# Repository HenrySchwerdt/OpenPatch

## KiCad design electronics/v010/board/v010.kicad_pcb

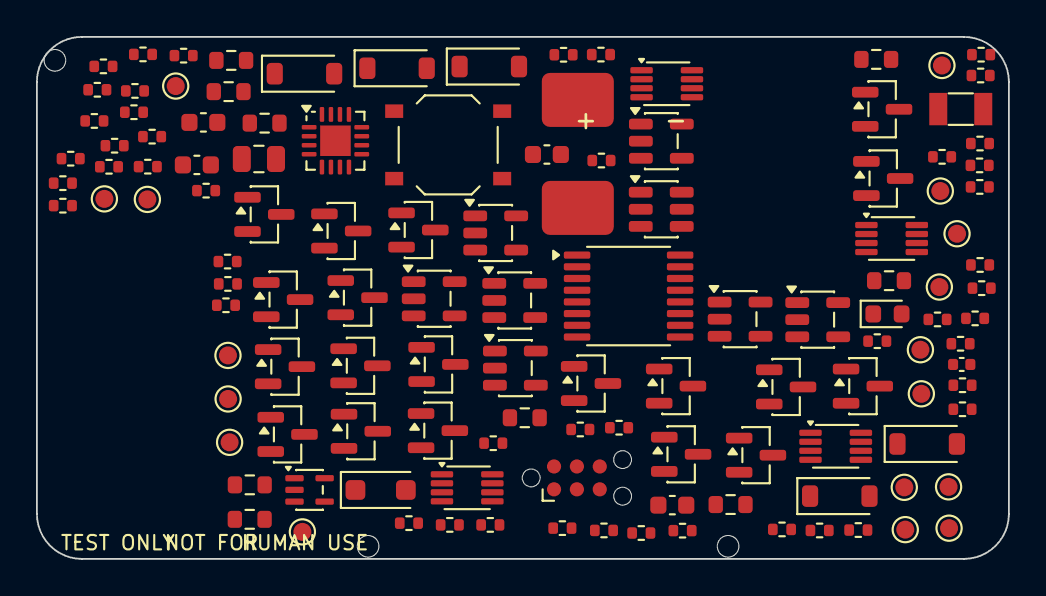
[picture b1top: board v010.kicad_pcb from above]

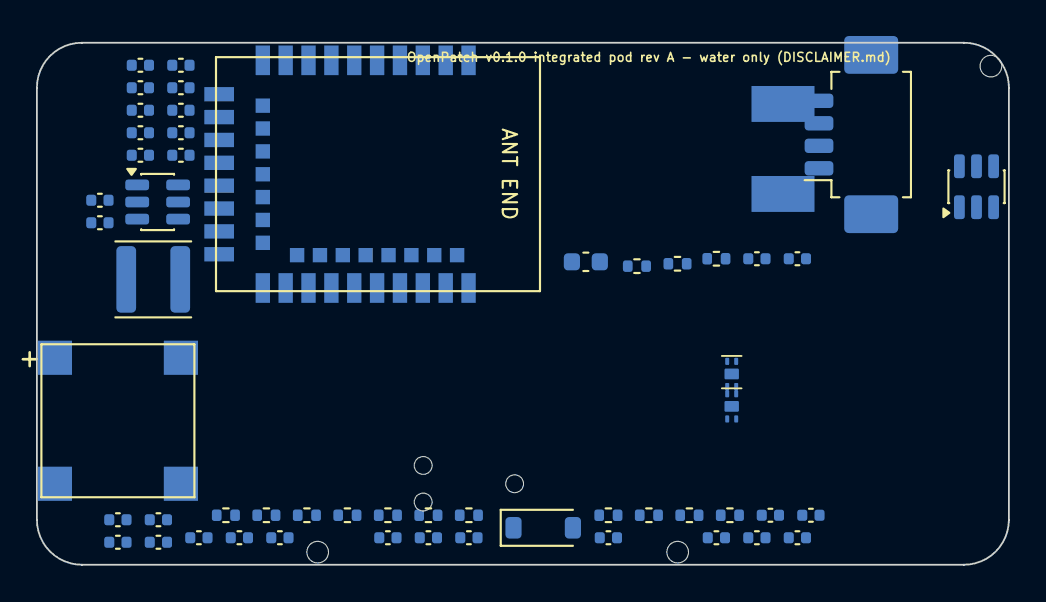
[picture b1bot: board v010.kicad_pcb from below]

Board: 4 copper layers, 54.0 x 29.0 mm, 185 parts (56 on the bottom side), 95 nets, no tracks yet.

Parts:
BZ1: MLT-8530; Buzzer_MLT-8530_8.5x8.5
C1, C10, C11, C14, C15, C19, C23, C25, C26, C28, C29, C30, C34, C35, C36, C37, C41, C42: 100nF; C_0402_1005Metric
C2, C8, C9: 4.7uF; C_0402_1005Metric
C3, C4: 15pF; C_0402_1005Metric
C5, C7, C22, C24: 10uF; C_0603_1608Metric
C6, C33: 1uF; C_0402_1005Metric
C16, C17, C20, C27, C32: 10nF; C_0402_1005Metric
C21: 22uF; C_0805_2012Metric
C31: 10uF (DNP); C_0603_1608Metric
D1, D5, D7: 1N4148W; D_SOD-123
D2, D4: B5819W SL; D_SOD-123
D3: SMF5.0A; D_SOD-123F
D6: B5819W SL (DNP); D_SOD-123
H1, H2, H3: NPTH 1.2; NPTH_1.2mm
J1: PicoBlade A1251WR-S-4P; Molex_PicoBlade_53261-0471_1x04-1MP_P1.25mm_Horizontal
J2: TC2030-IDC-NL (pads); Tag-Connect_TC2030-IDC-NL_2x03_P1.27mm_Vertical
L1: 4.7uH 4x4 (DNP); L_APV_ANR4018
LD1: red status; LED_0603_1608Metric
PAD1: charge pad +; Charge_Pad_4x3
PAD2: charge pad -; Charge_Pad_4x3
Q1, Q4, Q15: AO3401A; SOT-23
Q2, Q5, Q6, Q7, Q7B, Q8, Q10, Q11, Q12, Q13, Q14, Q16, Q17, Q18, Q19: 2N7002; SOT-23
R1, R5, R6, R7, R9, R10, R12, R15, R16, R17, R18, R21, R22, R28, R29, R32, R37, R39, R43, R46, R51, R53, R54, R57, R58, R61, R69, R72, R73: 100k; R_0402_1005Metric
R2, R70: 22R; R_0402_1005Metric
R3, R36: 47k; R_0402_1005Metric
R4: 3.3k; R_0402_1005Metric
R8, R11, R26, R40, R41, R42, R47, R48: 10k; R_0402_1005Metric
R13, R62: 0R; R_0603_1608Metric
R14, R33, R63: 0R DNP; R_0603_1608Metric
R19, R20: 4.7M; R_0402_1005Metric
R24, R25, R71, R75: 100R; R_0402_1005Metric
R27: 22k; R_0402_1005Metric
R30, R52, R74: 1k; R_0402_1005Metric
R31, R67, R68: 4.7k; R_0402_1005Metric
R34, R35: 1.0R; R_0603_1608Metric
R38: 5.1k; R_0402_1005Metric
R44: 0.22R; R_0603_1608Metric
R45: 0R bypass; R_0603_1608Metric
R49, R50, R59, R60: 1M; R_0402_1005Metric
R55: 220k (DNP); R_0402_1005Metric
R56: 30k (DNP); R_0402_1005Metric
RT1: NTC 10k NCP15XH103F03RC; C_0402_1005Metric
SP1, SP2: BWCD-L3.5W2.0H1.0 spring; Spring_Contact_3.5x2.0
SW1: TS-1187A-B-A-B; SW_Push_1P1T_XKB_TS-1187A
TP1: GND; TestPoint_Pad_D1.0mm
TP2: 3V3; TestPoint_Pad_D1.0mm
TP3: VBAT; TestPoint_Pad_D1.0mm
TP4: VMOT; TestPoint_Pad_D1.0mm
TP5: PGATE; TestPoint_Pad_D1.0mm
TP6: LATCH_Q; TestPoint_Pad_D1.0mm
TP7: MCU_EN; TestPoint_Pad_D1.0mm
TP8: DOCKED_H; TestPoint_Pad_D1.0mm
TP9: ARM_CLK; TestPoint_Pad_D1.0mm
TP10: LATCH_CLR_N; TestPoint_Pad_D1.0mm
TP11: NRST; TestPoint_Pad_D1.0mm
TP12: STCK_DRV; TestPoint_Pad_D1.0mm
TP13: WIN; TestPoint_Pad_D1.0mm
TP14: HWA_FULL; TestPoint_Pad_D1.0mm
TP15: OC_OK; TestPoint_Pad_D1.0mm
TP16: INA_OUT; TestPoint_Pad_D1.0mm
TP17: VCHG; TestPoint_Pad_D1.0mm
U1: E73-2G4M08S1C; Ebyte_E73-2G4M08S1C_13x18
U2: XC6206P332MR-G; SOT-23
U3: MCP73832T-2ACI/OT; SOT-23-5
U4A, U4B: DRV5032AJDMRR; DRV5032_X2SON-4_DMR0004B
U5: TPL5010DDCR; SOT-23-6
U6, U10, U12, U13: SN74AUP1G74DCUR; VSSOP-8_2.3x2mm_P0.5mm
U7: STSPIN220; QFN-16-1EP_3x3mm_P0.5mm_EP1.7x1.7mm
U8: MT3608 (DNP); SOT-23-6
U9: INA180A1IDBVR; SOT-23-5
U10T: TMAG5273A1QDBVR; SOT-23-6
U11: TLV7011DCKR; SOT-353_SC-70-5
U14: TP74AUP1G17S5; SOT-23-5
U15: SN74LV4040APWR; TSSOP-16_4.4x5mm_P0.65mm
U16, U18, U19: TP74AUP1G08S5; SOT-23-5
U17: TP74AUP1G32S5; SOT-23-5
Y1: 32.768kHz 12.5pF; Crystal_SMD_3215-2Pin_3.2x1.5mm

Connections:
3V3: C1.1, C2.1, C7.1, C14.1, C28.1, C29.1, C34.1, C35.1, C36.1, C37.1, C41.1, J2.1, R1.1, R12.1, R19.1, R20.1, R21.1, R28.2, R40.1, R49.1, R61.1, R67.1, R68.1, R69.1, R73.1, TP2.1, U1.19, U2.2, U4A.1, U4B.1, U5.1, U6.2, U6.7, U6.8, U10.7, U10.8, U10T.4, U11.5, U12.2, U12.7, U12.8, U13.2, U13.7, U13.8, U14.5, U15.16, U16.5, U17.5, U18.5, U19.5
ARM_CLK: R29.1, TP9.1, U1.32, U6.1, U13.1
BLD: Q17.3, R24.2, R25.2
BST_FB: R55.2, R56.1, U8.3
BST_SW: D6.2, L1.2, U8.1
BTN_N: C42.1, R73.2, SW1.1, U1.28
BUZ_PWM: R71.1, U1.38
BZ_D: Q19.3, R70.2
BZ_G: Q19.1, R71.2, R72.1
BZ_N: BZ1.2, D7.2, R70.1
CHG_P2: R3.2, R4.1
CHG_PAD: D3.1, PAD1.1, R2.1
CHG_PROG: R3.1, U3.5
CHG_R: D4.2, R2.2
CHG_STAT: U1.42, U3.1
CH_TOP: Q5.3, R11.2
CNT_CLK: U15.10, U19.4
DIR_INV: Q11.3, R12.2, R14.1, R62.1
DIR_REV: Q10.1, R13.2, R14.2, R15.1, U17.1
DOCKED_H: Q6.1, Q7.3, Q7B.3, Q12.3, R21.2, TP8.1, U1.10
DOCK_N: Q7.1, R19.2, U1.3, U4A.4
DOCK_NB: Q7B.1, R20.2, U4B.4
DOCK_TEST: Q12.1, R22.1, U1.2
DONE_PULSE: C16.2, R30.1, U10.1
DONE_TPL: R32.1, R33.2, U5.4, U10.5
FWD: R62.2, R63.2, U19.2
GND: C1.2, C2.2, C3.2, C4.2, C5.2, C6.2, C7.2, C8.2, C9.2, C10.2, C14.2, C15.2, C17.2, C19.2, C20.2, C21.2, C22.2, C23.2, C24.2, C25.2, C26.2, C27.2, C28.2, C29.2, C30.2, C31.2, C32.2, C33.2, C34.2, C35.2, C36.2, C37.2, C41.2, C42.2, D3.2, J2.5, PAD2.1, Q2.2, Q6.2, Q7.2, Q7B.2, Q10.2, Q11.2, Q12.2, Q14.2, Q16.2, Q17.2, Q18.2, Q19.2, R4.2, R7.2, R15.2, R16.2, R17.2, R18.2, R22.2, R26.2, R27.2, R29.2, R30.2, R32.2, R34.2, R35.2, R36.2, R38.2, R39.2, R41.2, R42.2, R43.2, R46.2, R51.2, R53.2, R56.2, R58.2, R72.2, R75.2, RT1.2, SP2.1, SW1.2, TP1.1, U1.5, U1.21, U1.24, U2.1, U3.2, U4A.2, U4A.5, U4B.2, U4B.5, U5.2, U6.4, U7.7, U7.17, U8.2, U9.2, U10.4, U10T.2, U10T.3, U11.2, U12.4, U13.4, U14.3, U15.8, U16.3, U17.3, U18.3, U19.3
HWA_FULL: Q18.1, TP14.1, U1.9, U15.2
HWA_FULL_N: Q18.3, R61.2, U16.2
HWA_X: U16.4, U17.2
HWA_Y: U17.4, U18.2
I2C_SCL: R68.2, U1.14, U10T.1
I2C_SDA: R67.2, U1.12, U10T.6
INA_OUT: R46.1, R47.1, R48.1, TP16.1, U9.1
I_SENSE: C26.1, R47.2, U1.7
LATCH_CLR_N: C15.1, D2.2, R28.1, TP10.1, U1.34, U6.6
LATCH_Q: Q5.1, R17.1, TP6.1, U1.33, U6.5
LD1_K: LD1.1, R75.1
LED_A: LD1.2, R74.2
LED_ST: R74.1, U1.36
MCU_EN: D5.1, Q8.1, R18.1, R54.1, TP7.1, U1.35
MODE1_L: R41.1, U7.16
MODE2_L: R42.1, U7.15
MOT_A1: J1.4, U7.3
MOT_A2: J1.2, U7.5
MOT_B1: J1.3, U7.10
MOT_B2: J1.1, U7.8
MOT_DIR: Q11.1, R13.1, R16.1, R63.1, U1.22, U7.1
MOT_EN_FAULT: C20.1, R40.2, U1.17, U7.13
MOT_REF: C19.1, R37.2, R38.1, U7.11
MOT_STBY: R37.1, R39.1, U1.1, U7.14
NRST: D2.1, J2.3, R1.2, TP11.1, U1.26, U5.6
NTC: R8.2, RT1.1, U1.8
OC_CLR_N: C30.1, D5.2, R54.2, U12.6
OC_CMP: U11.1, U12.1
OC_IN: C27.1, R48.2, U11.3
OC_OK: Q13.1, TP15.1, U1.41, U12.3
OC_REF: R49.2, R50.1, R52.2, U11.4
OC_REF2: R50.2, R51.1
OC_TEST: Q14.1, R53.1, U1.16
OC_TEST_D: Q14.3, R52.1
PGATE: C11.1, Q4.1, Q15.1, Q16.1, Q17.1, R9.2, R10.2, R11.1, TP5.1
PGATE_MON: Q16.3, U1.43
PG_MID1: Q5.2, Q8.3
PG_MID2: Q8.2, Q13.3
PG_MID2A: Q6.3, Q10.3, Q13.2
SENSE_EN: Q2.1, R8.1, U1.40
SNSA: R34.1, U7.4
SNSB: R35.1, U7.9
SP_G: Q1.1, Q2.3, R5.2
STCK_DRV: TP12.1, U7.2, U18.4, U19.1
STCK_MCU: R43.1, U1.20, U18.1
SWDCLK: J2.4, U1.39
SWDIO: J2.2, U1.37
TMAG_INT: R69.2, U10T.5
TN: C33.1, R59.2, R60.2, U14.2
TOFF: R36.1, U7.12
TS: U13.6, U14.4
VBAT: BZ1.1, C5.1, C6.1, C9.1, C11.2, D7.1, Q1.2, Q4.2, R5.1, R9.1, R10.1, SP1.1, TP3.1, U2.3, U3.3
VBAT_SENSE: C10.1, R6.2, R7.1, U1.15
VBAT_SW: Q1.3, R6.1
VCHG: C8.1, D4.1, TP17.1, U3.4
VMOT: C21.1, C22.1, C23.1, R24.1, R25.1, R44.2, R57.1, TP4.1, U7.6, U9.4
VMOT_A: Q4.3, Q15.2
VMOT_PRE: C31.1, D6.1, R44.1, R45.2, R55.1, U9.3
VMOT_RAW: C24.1, C25.1, L1.1, Q15.3, R45.1, U8.4, U8.5, U9.5
VMOT_SENSE: C32.1, R57.2, R58.1, U1.18
WAKE_CLR: C17.1, D1.1, R31.1, U10.6
WDT_DELAY: R26.1, R27.1, U5.3
WDT_DONE: C16.1, R33.1, U1.4
WDT_WAKE: D1.2, R31.2, U1.30, U5.5, U10.2
WIN: TP13.1, U1.6, U13.5, U16.1
WIN_N: R59.1, R60.1, U13.3, U15.11
XL1: C3.1, U1.11, Y1.1
XL2: C4.1, U1.13, Y1.2

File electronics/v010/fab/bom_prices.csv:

LCSC,Value,Qty/board,Unit USD (tier 1),JLC stock,Basic,Refs
C356849,E73-2G4M08S1C,1,7.6971,1,ext,U1
C1525,100nF,18,0.0024,34619114,basic,C1 C10 C11 C14 C15 C19 C23 C25 C26 C28 C29 C30 C34 C35 C36 C37 C41 C42
C23733,4.7uF,3,0.0077,983783,basic,C2 C8 C9
C32346,32.768kHz 12.5pF,1,0.15,663204,basic,Y1
C1548,15pF,2,0.0026,1413765,basic,C3 C4
C25741,100k,29,0.0009,8479183,basic,R1 R5 R6 R7 R9 R10 R12 R15 R16 R17 R18 R21 R22 R28 R29 R32 R37 R39 R43 R46 R51 R53 R54 R57 R58 R61 R69 R72 R73
C2826547,BWCD-L3.5W2.0H1.0 spring,2,0.0763,8081,ext,SP1 SP2
C19702,10uF,4,0.0167,10348979,basic,C5 C7 C22 C24
C5446,XC6206P332MR-G,1,0.138,429396,basic,U2
C52923,1uF,2,0.0055,9476015,basic,C6 C33
C193402,SMF5.0A,1,0.0284,453722,ext,D3
C25092,22R,2,0.001,4369824,basic,R2 R70
C8598,B5819W SL,2,0.0256,854955,basic,D4 D2
C38066,MCP73832T-2ACI/OT,1,0.9593,8016,ext,U3
C25792,47k,2,0.0019,5404806,basic,R3 R36
C25890,3.3k,1,0.0036,1526817,basic,R4
C15127,AO3401A,3,0.0855,1342147,basic,Q1 Q4 Q15
C8545,2N7002,15,0.0158,6047282,basic,Q2 Q5 Q8 Q13 Q6 Q10 Q11 Q7 Q7B Q12 Q16 Q17 Q14 Q18 Q19
C25744,10k,8,0.0015,35956809,basic,R8 R11 R26 R40 R41 R42 R47 R48
C77131,NTC 10k NCP15XH103F03RC,1,0.0164,292530,ext,RT1
C21189,0R,3,0.0021,15907781,basic,R13 R45 R62
C2152498,DRV5032AJDMRR,2,0.3744,0,ext,U4A U4B
C26091,4.7M,2,0.0008,9038,ext,R19 R20
C25076,100R,4,0.0012,10088994,basic,R24 R25 R71 R75
C473912,TPL5010DDCR,1,0.3536,59721,ext,U5
C25768,22k,1,0.001,1186378,basic,R27
C140267,SN74AUP1G74DCUR,4,0.6745,17358,ext,U6 U10 U12 U13
C15195,10nF,5,0.0037,5496842,basic,C16 C17 C20 C27 C32
C11702,1k,3,0.0013,29992555,basic,R30 R52 R74
C25900,4.7k,3,0.0017,12654925,basic,R31 R67 R68
C81598,1N4148W,3,0.0124,2921267,basic,D1 D5 D7
C2150516,STSPIN220,1,1.9612,270,ext,U7
C174300,1.0R,2,0.0029,150749,ext,R34 R35
C25905,5.1k,1,0.0014,4287672,basic,R38
C45783,22uF,1,0.1975,3628752,basic,C21
C225113,PicoBlade A1251WR-S-4P,1,0.1101,13833,ext,J1
C326952,0.22R,1,0.019,10537,ext,R44
C122228,INA180A1IDBVR,1,0.288,55831,ext,U9
C193688,TLV7011DCKR,1,0.5566,10273,ext,U11
C26083,1M,4,0.0011,2766372,basic,R49 R50 R59 R60
C49333201,TP74AUP1G17S5,1,0.0537,3000,ext,U14
C180412,SN74LV4040APWR,1,1.1901,271,ext,U15
C48886815,TP74AUP1G08S5,3,0.0603,1932,ext,U16 U18 U19
C49333203,TP74AUP1G32S5,1,0.0537,2930,ext,U17
C3716049,TMAG5273A1QDBVR,1,3.5703,3401,ext,U10T
C94599,MLT-8530,1,0.197,114212,ext,BZ1
C318884,TS-1187A-B-A-B,1,0.0215,757186,basic,SW1
C2286,red status,1,0.0077,8591521,basic,LD1

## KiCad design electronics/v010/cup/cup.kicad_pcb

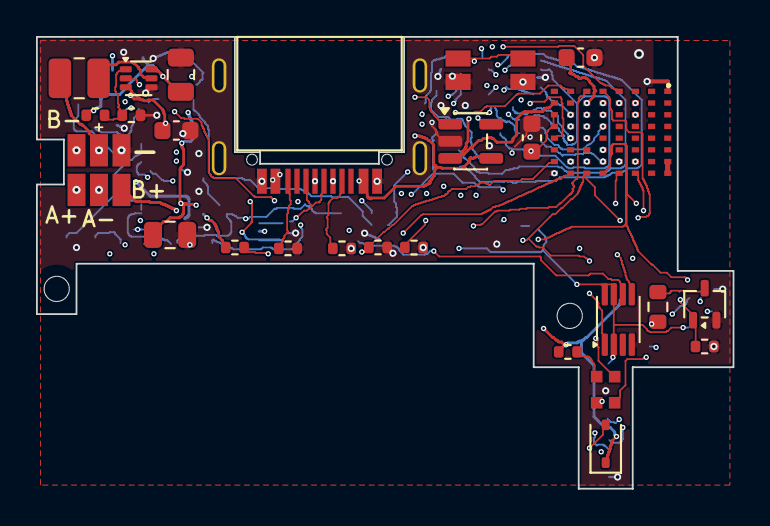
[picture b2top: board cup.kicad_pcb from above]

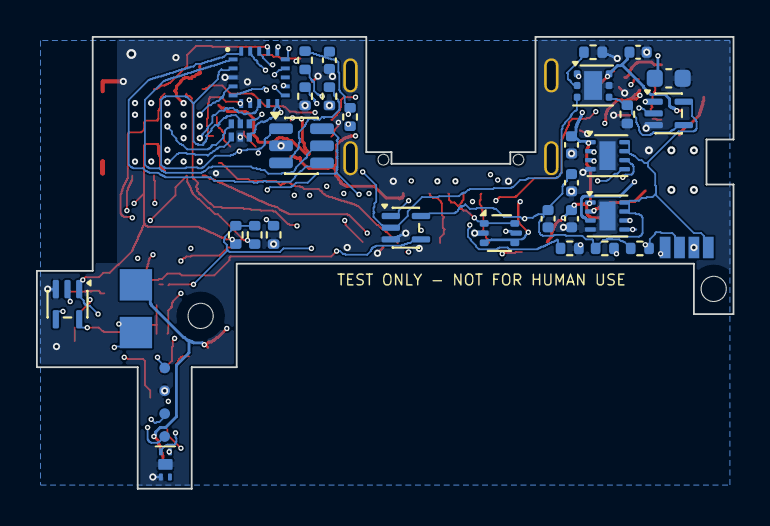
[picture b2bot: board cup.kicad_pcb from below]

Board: 6 copper layers, 38.7 x 25.1 mm, 72 parts (39 on the bottom side), 57 nets.

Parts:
BZ1: FUET-4020 SMD magnetic sounder; BZ_4020
C5: 10uF; C_0603_1608Metric
C19, C20, C50, C60, C61, C62: 100nF; C_0402_1005Metric
C21: 22uF; C_0805_2012Metric
C70: 4.7uF 16V 0603; C_0603_1608Metric
C71: 10uF 10V 0603; C_0603_1608Metric
CB1: 22uF 25V X5R 0805; C_0805_2012Metric
CU1: 10uF; C_0603_1608Metric
D6: 1N4148WS (sounder flyback); D_SOD-323
H1, H2: screw hole d1.4
JU1: USB-C 16P sink-board TYPE-C-31-M-14; USB_C_HRO_31_M_14
L1: 1uH 2520 (WPN252012E1R0MT); L_1008_2520Metric
LD1: RGB LED SZYY1615RGB-B (common anode); LED_RGB_1615_4P
MP1: motor lead pad A+; Wire_Pad_1.0x1.8
MP2: motor lead pad A-; Wire_Pad_1.0x1.8
MP3: motor lead pad B+; Wire_Pad_1.0x1.8
MP4: motor lead pad B-; Wire_Pad_1.0x1.8
QBA: 2N7002W; SOT-323_SC-70
R3, R91: 47k; R_0402_1005Metric
R16, R18, R29, R82, R90, R92: 100k; R_0402_1005Metric
R26: 6.8k; R_0402_1005Metric
R55: 220k; R_0402_1005Metric
R56: 30k; R_0402_1005Metric
R57, R58: 10k; R_0402_1005Metric
R74: 1k; R_0402_1005Metric
RBZ: 22R 0603; R_0603_1608Metric
RDA: 100k; R_0402_1005Metric
RDK: 100k; R_0402_1005Metric
RI1, RI2: 4.7k; R_0402_1005Metric
RNR: 100k; R_0402_1005Metric
RU1, RU2: 5.1k; R_0402_1005Metric
SP1: cell lead pad +; Wire_Pad_1.0x1.8
SP2: cell lead pad -; Wire_Pad_1.0x1.8
SW1: SKSCLAE010 side tact; SW_SKSCLAE010
TL1: REAR strip pad (3V3); FPC_Pad_1.2x0.6
TL2: REAR strip pad (GND); FPC_Pad_1.2x0.6
TL3: REAR strip pad (I2C_SDA); FPC_Pad_1.2x0.6
TL4: REAR strip pad (I2C_SCL); FPC_Pad_1.2x0.6
TPR1: recovery pad SWDIO; TP_Pad_D0.6
TPR2: recovery pad SWDCLK; TP_Pad_D0.6
TPR3: recovery pad GND; TP_Pad_D0.6
TPR4: recovery pad 3V3; TP_Pad_D0.6
U1: HJ-840 nRF52840 SiP; HJ840
U3: MCP73832T-2ACI/OT; SOT-23-5
U4A: DRV5032FADMRR; DRV5032_X2SON-4_DMR0004B
U5: TPL5010DDCR; SOT-23-6
U6: SN74AUP1G74DCUR; VSSOP-8_2.3x2mm_P0.5mm
U7A, U7B: DRV8838DSGR; Texas_DSG0008A_WSON-8-1EP_2x2mm_P0.5mm_EP0.9x1.6mm
U8: TPS61023DRLR; SOT-563
U20: TPS2553DRVR; WSON-6-1EP_2x2mm_P0.65mm_EP1x1.6mm
U30: STM32C011F4U6; UFQFPN-20_3x3_P0.5
U32, U34: SN74AUP1G08DCKR (AND); SOT-353_SC-70-5
U33: 74AUP1G86GW-TP (XOR); SOT-353_SC-70-5
U36: EM74AUP1G11GM (AND3); UFDFN-6_1.45x1.0_P0.5
UU1: USBLC6-2P6; SOT-666

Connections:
3V3: C19.1, C20.1, C50.1, C70.1, R16.1, R92.1, RDK.1, RI1.1, RI2.1, RNR.1, TL1.1, TPR4.1, U1.H3, U1.H4, U4A.1, U5.1, U6.2, U6.7, U6.8, U7A.7, U7A.8, U7B.7, U7B.8, U30.2, U32.5, U33.5, U34.5, U36.5
AENBL: U1.F5, U7A.5
ANT: U1.A7, U1.A8
APHASE: U1.H5, U7A.6, U30.6
ARM_CLK: R29.1, U1.G7, U6.1, U30.5
BENBL: U1.E6, U7B.5
BPHASE: U1.F4, U7B.6, U30.16
BST_FB: R55.2, R56.1, U8.1
BST_SW: L1.2, U8.5
BTN_N: SW1.1, SW1.2, U1.D2
BUZ_A: QBA.1, RDA.1, U1.C7
CC1: JU1.A5, RU1.1
CC2: JU1.B5, RU2.1
CHG_PROG: R3.1, U3.5
CHG_STAT: U1.G4, U3.1
DOCK_N: RDK.2, U1.E8, U4A.4, U30.18, U33.1
DOCK_XOR: U33.4, U34.2
GND: C5.2, C19.2, C20.2, C21.2, C50.2, C60.2, C61.2, C62.2, C70.2, C71.2, CB1.2, CU1.2, JU1.A1B12, JU1.B1A12, JU1.S, QBA.2, R3.2, R18.2, R26.2, R29.2, R56.2, R58.2, R82.2, R90.2, R91.2, RDA.2, RU1.2, RU2.2, SP2.1, SW1.3, SW1.4, TL2.1, TPR3.1, U1.A1, U1.H8, U3.2, U4A.2, U4A.5, U5.2, U6.4, U7A.4, U7A.9, U7B.4, U7B.9, U8.4, U20.5, U20.7, U30.3, U32.3, U33.3, U34.3, U36.2, UU1.2
I2C_SCL: RI2.2, TL4.1, U1.G8
I2C_SDA: RI1.2, TL3.1, U1.F7
ILIM: R91.1, U20.2
LATCH_CLR_N: U6.6, U32.4
LATCH_Q: U1.E7, U6.5, U36.1
LED_A: LD1.4, R74.2
LED_B: LD1.3, U1.D7
LED_G: LD1.2, U1.C8
LED_R: LD1.1, U1.D8
MCU_EN: R18.1, U1.E4, U30.19, U36.6
MOT_A1: MP1.1, U7A.2
MOT_A2: MP2.1, U7A.3
MOT_ALLOW: R90.1, U20.4, U34.4
MOT_B1: MP3.1, U7B.2
MOT_B2: MP4.1, U7B.3
MOT_FWD: R16.2, U1.F8, U30.7, U33.2
NRST: U1.E1, U30.12
OC_OK: R92.2, U1.G5, U20.3, U30.8, U32.2
PERM_L: U34.1, U36.4
PZ_A: QBA.3, RBZ.2
PZ_C: BZ1.2, D6.2, RBZ.1
SUP_BOOT0: U1.D1, U30.17
SUP_DONE: U5.4, U30.20
SUP_NRST: RNR.2, U1.G3, U5.6, U30.4, U32.1
SUP_OK: U1.F3, U30.11
SUP_PERMIT: R82.1, U8.2, U30.10, U36.3
SUP_RXD: U1.E2, U30.15
SUP_TXD: U1.E3, U30.14
SUP_WAKE: U5.5, U30.1
SWDCLK: TPR2.1, U1.C3
SWDIO: TPR1.1, U1.C2
USB_DM: JU1.A7, JU1.B7, U1.G1, UU1.3, UU1.4
USB_DP: JU1.A6, JU1.B6, U1.F1, UU1.1, UU1.6
VBAT: BZ1.1, C5.1, C71.1, D6.1, L1.1, R74.1, SP1.1, U1.H2, U3.3, U8.3
VBUS_P: CU1.1, JU1.A4B9, JU1.B4A9, U1.F2, U3.4, UU1.5
VMOT: C21.1, C61.1, C62.1, R57.1, U7A.1, U7B.1, U20.1
VMOT_PRE: C60.1, CB1.1, R55.1, U8.6, U20.6
VMOT_SENSE: R57.2, R58.1, U1.H7
WDT_DELAY: R26.1, U5.3

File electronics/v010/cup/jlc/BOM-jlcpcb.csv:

Comment,Designator,Footprint,LCSC Part #
FUET-4020 SMD magnetic sounder,BZ1,BZ_4020,C391027
10uF,"C5,C71,CU1",C_0603_1608Metric,C19702
100nF,"C19,C20,C50,C60,C61,C62",C_0402_1005Metric,C1525
22uF,"C21,CB1",C_0805_2012Metric,C45783
4.7uF 16V 0603,C70,C_0603_1608Metric,C19666
1N4148WS (sounder flyback),D6,D_SOD-323,C2128
USB-C 16P sink-board TYPE-C-31-M-14,JU1,USB_C_HRO_31_M_14,C223907
1uH 2520 (WPN252012E1R0MT),L1,L_1008_2520Metric,C370610
RGB LED SZYY1615RGB-B (common anode),LD1,LED_RGB_1615_4P,C3029071
2N7002W,QBA,SOT-323_SC-70,C232391
47k,"R3,R91",R_0402_1005Metric,C25792
100k,"R16,R18,R29,R82,R90,R92,RDA,RDK,RNR",R_0402_1005Metric,C25741
6.8k,R26,R_0402_1005Metric,C25917
220k,R55,R_0402_1005Metric,C25767
30k,R56,R_0402_1005Metric,C25776
10k,"R57,R58",R_0402_1005Metric,C25744
1k,R74,R_0402_1005Metric,C11702
22R 0603,RBZ,R_0603_1608Metric,C23345
4.7k,"RI1,RI2",R_0402_1005Metric,C25900
5.1k,"RU1,RU2",R_0402_1005Metric,C25905
SKSCLAE010 side tact,SW1,SW_SKSCLAE010,C130445
HJ-840 nRF52840 SiP,U1,HJ840,C50052094
MCP73832T-2ACI/OT,U3,SOT-23-5,C38066
TPL5010DDCR,U5,SOT-23-6,C473912
SN74AUP1G74DCUR,U6,VSSOP-8_2.3x2mm_P0.5mm,C140267
TPS61023DRLR,U8,SOT-563,C919459
TPS2553DRVR,U20,WSON-6-1EP_2x2mm_P0.65mm_EP1x1.6mm,C138719
STM32C011F4U6,U30,UFQFPN-20_3x3_P0.5,C5456188
SN74AUP1G08DCKR (AND),"U32,U34",SOT-353_SC-70-5,C507223
74AUP1G86GW-TP (XOR),U33,SOT-353_SC-70-5,C48995440
EM74AUP1G11GM (AND3),U36,UFDFN-6_1.45x1.0_P0.5,C54929506
DRV5032FADMRR,U4A,DRV5032_X2SON-4_DMR0004B,C2152496
DRV8838DSGR,"U7A,U7B",Texas_DSG0008A_WSON-8-1EP_2x2mm_P0.5mm_EP0.9x1.6mm,C86667
USBLC6-2P6,UU1,SOT-666,C2827693

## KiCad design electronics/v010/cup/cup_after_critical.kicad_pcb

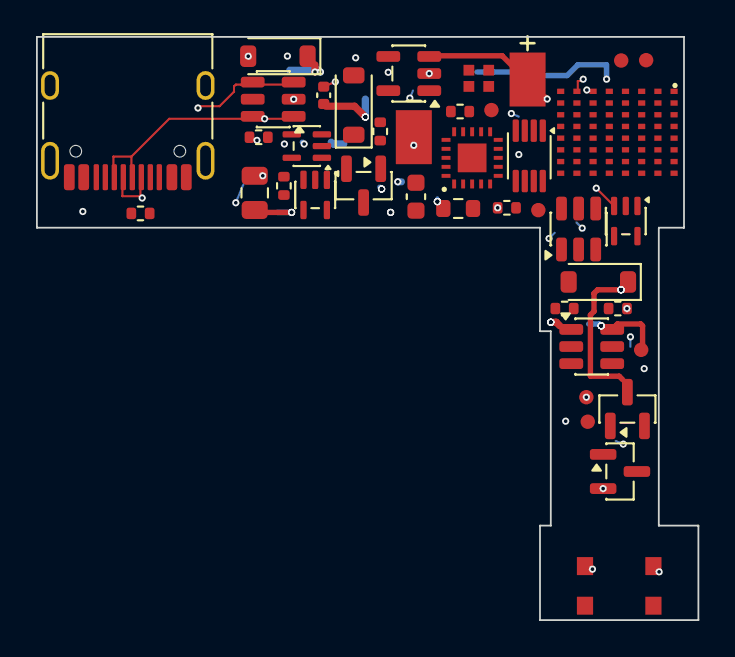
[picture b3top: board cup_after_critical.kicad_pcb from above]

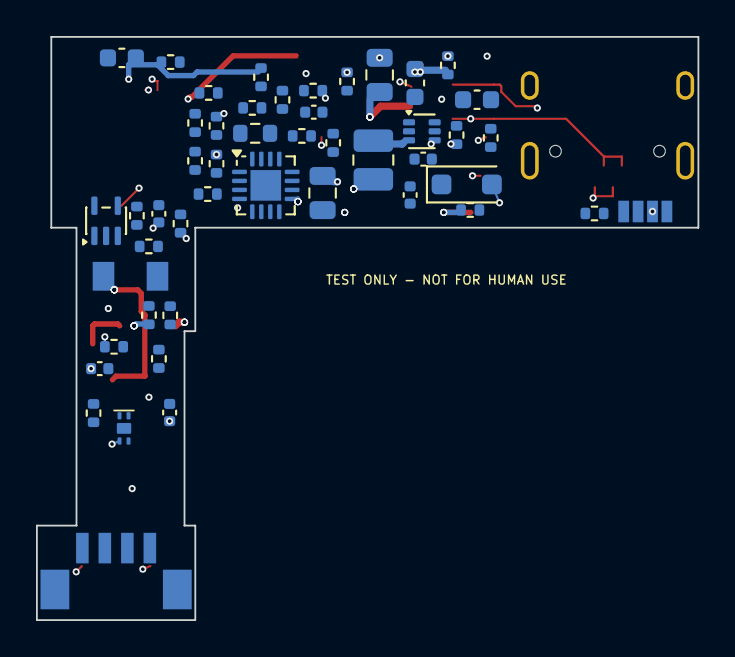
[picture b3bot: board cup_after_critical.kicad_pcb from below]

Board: 6 copper layers, 36.8 x 32.4 mm, 91 parts (51 on the bottom side), 63 nets.

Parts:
BZ1: FUET-4020 SMD magnetic sounder; BZ_4020
C1, C10, C19, C50, C60: 100nF; C_0402_1005Metric
C5, C7, C31: 10uF; C_0603_1608Metric
C21: 22uF; C_0805_2012Metric
CB1, CB2: 22uF 6.3V X5R 0805; C_0805_2012Metric
CU1: 10uF; C_0603_1608Metric
D5: 1N4148W; D_SOD-123
D6: 1N4148W (sounder flyback); D_SOD-123
DU1: SMF5.0A TVS; D_SOD-123F
DZ1: BZT52C6V2 (VMOT overvoltage clamp); D_SOD-123
J1: PicoBlade A1251WR-S-4P (CJT, plug of the NFP-608 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; A1251WR-S-4P
J10: SWD pad SWDIO; TP_Pad_D0.8
J11: SWD pad SWDCLK; TP_Pad_D0.8
J12: SWD pad NRST; TP_Pad_D0.8
J13: SWD pad GND; TP_Pad_D0.8
J14: SWD pad 3V3; TP_Pad_D0.8
JU1: USB-C receptacle (proxy: TYPE-C-31-M-12; IPX7 par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; USB_C_Receptacle_HRO_TYPE-C-31-M-12
L1: 1uH 2520 (WPN252012E1R0MT); L_1008_2520Metric
LD1: RGB LED SZYY1615RGB-B (common anode); LED_RGB_1615_4P
PI1, PI3: pi match shunt C (DNP); C_0402_1005Metric
PI2: pi match series 0R; R_0402_1005Metric
Q7: 2N7002; SOT-23
QBA: 2N7002; SOT-23
R1, R16, R18, R21, R29, R37, R39, R43, R57, R58, R79, R80, R81, R82, R90, R92: 100k; R_0402_1005Metric
R3, R36: 47k; R_0402_1005Metric
R6, R7: 1M; R_0402_1005Metric
R24, R25, R26, R40: 10k; R_0402_1005Metric
R34, R35: 1.0R; R_0603_1608Metric
R38: 5.1k; R_0402_1005Metric
R55: 220k; R_0402_1005Metric
R56: 30k; R_0402_1005Metric
R67, R68: 4.7k; R_0402_1005Metric
R74: 1k; R_0402_1005Metric
R91: 56k; R_0402_1005Metric
RDA: 100k; R_0402_1005Metric
RU1, RU2: 5.1k; R_0402_1005Metric
SP1: cell lead pad +; Wire_Pad_2.0x3.0
SP2: cell lead pad -; Wire_Pad_2.0x3.0
SW1: SKRPACE010 side tact; SW_SKRPACE010_4.2x3.2
TL1: REAR strip pad (3V3); FPC_Pad_1.2x0.6
TL2: REAR strip pad (GND); FPC_Pad_1.2x0.6
TL3: REAR strip pad (I2C_SDA); FPC_Pad_1.2x0.6
TL4: REAR strip pad (I2C_SCL); FPC_Pad_1.2x0.6
TP1: VMOT; TP_Pad_D0.8
TP2: STCK_DRV; TP_Pad_D0.8
U1: HJ-840 nRF52840 SiP; HJ840
U2: XC6206P332MR-G; SOT-23
U3: MCP73832T-2ACI/OT; SOT-23-5
U4A: DRV5032FADMRR; DRV5032_X2SON-4_DMR0004B
U5: TPL5010DDCR; SOT-23-6
U6: SN74AUP1G74DCUR; VSSOP-8_2.3x2mm_P0.5mm
U7: STSPIN220; QFN-16-1EP_3x3mm_P0.5mm_EP1.7x1.7mm
U8: TPS61023DRLR; SOT-563
U20: TPS2553DBVR; SOT-23-6
U30: STM32C011F4U6; UFQFPN-20_3x3_P0.5
U31: SN74AUP1G08DCKR; SOT-353_SC-70-5
U32, U34: TP74AUP1G08S5 (AND); SOT-353_SC-70-5
U33: TP74AUP1G32S5 (OR); SOT-353_SC-70-5
UU1: USBLC6-2SC6; SOT-23-6

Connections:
3V3: C1.1, C7.1, C50.1, J14.1, R1.1, R21.1, R40.1, R67.1, R68.1, R80.2, R92.1, TL1.1, U1.H2, U1.H3, U1.H4, U2.2, U4A.1, U5.1, U6.2, U6.7, U6.8, U30.4, U31.5, U32.5, U33.5, U34.5
ANT_A: PI1.1, PI2.1, U1.A7
ANT_B: PI2.2, PI3.1, U1.A8
ARM_CLK: R29.1, U1.E5, U6.1, U30.7
BST_FB: R55.2, R56.1, U8.6
BST_SW: L1.2, U8.3
BTN_N: SW1.1, SW1.2, U1.B8
BUZ_A: QBA.1, RDA.1, U1.F6
CC1: JU1.A5, RU1.1
CC2: JU1.B5, RU2.1
CHG_PROG: R3.1, U3.5
CHG_STAT: D5.1, U1.G3, U3.1
DOCKED_H: Q7.3, R21.2, U1.D7, U30.20, U33.1
DOCK_N: Q7.1, U1.C8, U4A.4
DOCK_OR: U33.4, U34.2
GND: C1.2, C5.2, C7.2, C10.2, C19.2, C21.2, C31.2, C50.2, C60.2, CB1.2, CB2.2, CU1.2, DU1.2, DZ1.2, J13.1, JU1.A1, JU1.A12, JU1.B1, JU1.B12, JU1.SH, PI1.2, PI3.2, Q7.2, QBA.2, R3.2, R7.2, R16.2, R18.2, R24.2, R25.2, R26.2, R29.2, R34.2, R35.2, R36.2, R38.2, R39.2, R43.2, R56.2, R58.2, R79.2, R81.2, R82.2, R90.2, R91.2, RDA.2, RU1.2, RU2.2, SP2.1, SW1.3, SW1.4, TL2.1, U1.A1, U1.H8, U2.1, U3.2, U4A.2, U4A.5, U5.2, U6.4, U7.7, U7.15, U7.16, U7.17, U8.2, U20.2, U30.5, U30.21, U31.3, U32.3, U33.3, U34.3, UU1.2
I2C_SCL: R68.2, TL4.1, U1.D6
I2C_SDA: R67.2, TL3.1, U1.G7
ILIM: R91.1, U20.5
LATCH_CLR_N: U6.6, U32.4
LATCH_Q: U1.E7, U6.5, U34.1
LED_A: LD1.4, R74.2
LED_B: LD1.3, U1.E3
LED_G: LD1.2, U1.E2
LED_R: D5.2, LD1.1, U1.F3
MCU_EN: R18.1, U1.G8, U30.1
MOT_A1: J1.4, U7.3
MOT_A2: J1.2, U7.5
MOT_ALLOW: R90.1, U20.3, U34.4
MOT_B1: J1.3, U7.10
MOT_B2: J1.1, U7.8
MOT_DIR: R16.1, U1.F7, U7.1, U30.9, U33.2
MOT_EN_FAULT: R40.2, U1.G4, U7.13
MOT_REF: C19.1, R37.2, R38.1, U7.11
MOT_STBY: R37.1, R39.1, U1.F5, U7.14
NRST: J12.1, R1.2, U1.E1, U30.14
OC_OK: R92.2, U1.D8, U20.4, U30.10, U32.2
PZ_A: BZ1.2, D6.2, QBA.3
SNSA: R34.1, U1.E6, U7.4
SNSB: R35.1, U7.9
STCK_DRV: TP2.1, U7.2, U31.4
STCK_MCU: R43.1, U1.F8, U30.8, U31.1
SUP_BOOT0: R79.1, U1.E4, U30.19
SUP_DONE: U5.4, U30.2
SUP_NRST: R80.1, U1.E8, U5.6, U30.6, U32.1
SUP_OK: U1.F4, U30.13
SUP_PERMIT: R82.1, U8.1, U30.12
SUP_RXD: U1.G6, U30.17
SUP_STCK_EN: R81.1, U30.11, U31.2
SUP_TXD: U1.H5, U30.16
SUP_WAKE: U5.5, U30.3
SWDCLK: J11.1, U1.C3
SWDIO: J10.1, U1.C2
TOFF: R36.1, U7.12
USB_DM: JU1.A7, JU1.B7, U1.G1, UU1.3, UU1.4
USB_DP: JU1.A6, JU1.B6, U1.F1, UU1.1, UU1.6
VBAT: BZ1.1, C5.1, D6.1, L1.1, R6.1, R74.1, SP1.1, U2.3, U3.3, U8.4
VBAT_SENSE: C10.1, R6.2, R7.1, U1.G5
VBUS_P: CU1.1, DU1.1, JU1.A4, JU1.A9, JU1.B4, JU1.B9, U1.F2, U3.4, UU1.5
VMOT: C21.1, R25.1, R57.1, TP1.1, U7.6, U20.6
VMOT_PRE: C31.1, C60.1, CB1.1, CB2.1, DZ1.1, R24.1, R55.1, U8.5, U20.1
VMOT_SENSE: R57.2, R58.1, U1.H7
WDT_DELAY: R26.1, U5.3

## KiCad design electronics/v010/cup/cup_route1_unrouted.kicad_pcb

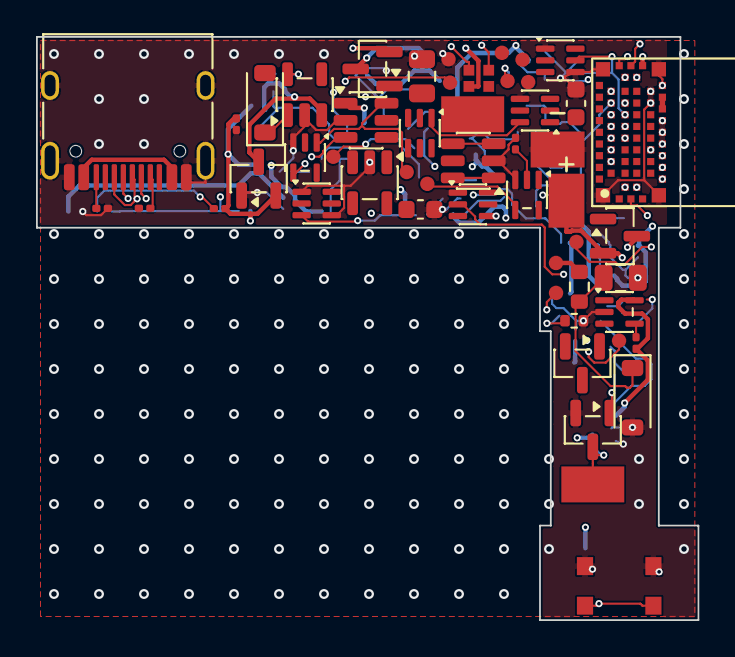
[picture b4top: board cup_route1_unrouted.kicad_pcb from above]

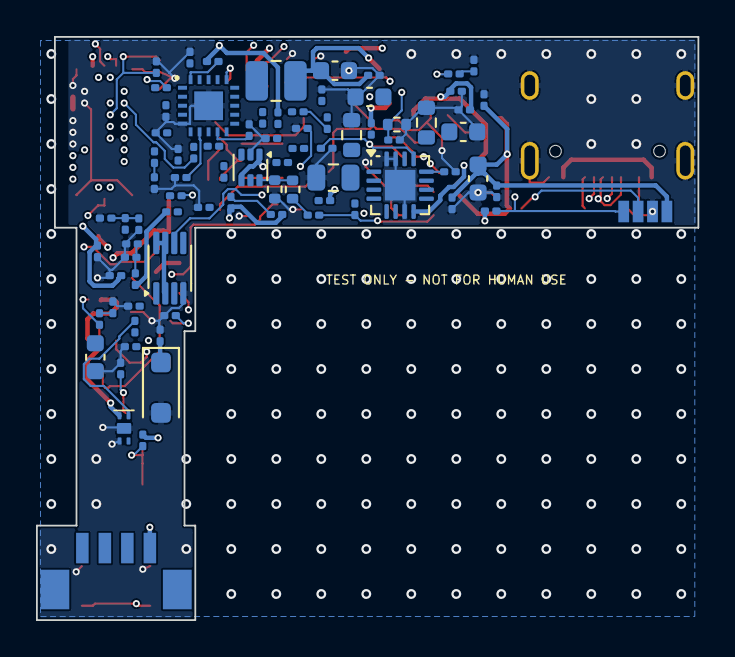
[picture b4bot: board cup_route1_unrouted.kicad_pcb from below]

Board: 6 copper layers, 36.8 x 32.4 mm, 136 parts (84 on the bottom side), 82 nets.

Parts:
C1, C10, C11, C14, C19, C23, C25, C28, C50, C52, C60: 100nF; C_0201_0603Metric
C2, C9: 4.7uF; C_0201_0603Metric
C5, C7, C22, C24, C31: 10uF; C_0603_1608Metric
C6, C51: 1uF; C_0201_0603Metric
C20, C27, C32: 10nF; C_0201_0603Metric
C21: 22uF; C_0603_1608Metric
CB1, CB2, CB3: 47uF 6.3V X5R 0805; C_0805_2012Metric
CU1: 10uF; C_0603_1608Metric
CU2: 1uF; C_0201_0603Metric
D5: 1N4148W; D_SOD-123
DU1: SMF5.0A TVS; D_SOD-123F
DZ1: BZT52C6V2 (VMOT overvoltage clamp); D_SOD-123
J1: PicoBlade A1251WR-S-4P (CJT, plug of the NFP-608 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; A1251WR-S-4P
J10: SWD pad SWDIO; TP_Pad_D0.8
J11: SWD pad SWDCLK; TP_Pad_D0.8
J12: SWD pad NRST; TP_Pad_D0.8
J13: SWD pad GND; TP_Pad_D0.8
J14: SWD pad SUP_SWDIO; TP_Pad_D0.8
J15: SWD pad SUP_SWDCLK; TP_Pad_D0.8
J16: SWD pad SUP_NRST; TP_Pad_D0.8
JU1: USB-C receptacle (proxy: TYPE-C-31-M-12; IPX7 par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; USB_C_Receptacle_HRO_TYPE-C-31-M-12
L1: 1uH 2520 (WPN252012E1R0MT); L_1008_2520Metric
LD1: RGB LED SZYY1615RGB-B (common anode); LED_RGB_1615_4P
PZ1: piezo spring pad A; Spring_Contact_3.5x2.0
PZ2: piezo spring pad B; Spring_Contact_3.5x2.0
Q4, Q15: AO3401A; SOT-23
QBB: 2N7002; SOT-23
QD1: 2N7002DW (QL + QS); SOT-363_SC-70-6
QD2: 2N7002DW (QE + Q12); SOT-363_SC-70-6
QD3: 2N7002DW (QD + Q17); SOT-363_SC-70-6
QD4: 2N7002DW (QR + Q17B); SOT-363_SC-70-6
QD5: 2N7002DW (Q7 + QBA); SOT-363_SC-70-6
QU1: AO3401A (ideal diode / reverse protect); SOT-23
R1, R9, R10, R16, R17, R18, R21, R22, R29, R37, R39, R43, R51, R57, R58, R80, R81, R82, R83, R85, R86: 100k; R_0201_0603Metric
R3, R36: 47k; R_0201_0603Metric
R4: 3.3k; R_0201_0603Metric
R6, R7, R19: 4.7M; R_0201_0603Metric
R11, R26, R40, R48, R84: 10k; R_0201_0603Metric
R24, R25: 100R; R_0201_0603Metric
R27: 22k; R_0402_1005Metric
R34, R35: 1.0R; R_0603_1608Metric
R38: 5.6k; R_0402_1005Metric
R44: 0.22R; R_0603_1608Metric
R49, R50: 1M; R_0201_0603Metric
R55: 220k; R_0402_1005Metric
R56: 30k; R_0402_1005Metric
R67, R68: 4.7k; R_0201_0603Metric
R74: 1k; R_0201_0603Metric
R75, R76: 470R; R_0201_0603Metric
RBA: 1k; R_0201_0603Metric
RBB: 1k; R_0201_0603Metric
RDA: 100k; R_0201_0603Metric
RDB: 100k; R_0201_0603Metric
RU1, RU2: 5.1k; R_0201_0603Metric
RU3: 100k; R_0201_0603Metric
SP1: cell lead pad +; Wire_Pad_2.0x3.0
SP2: cell lead pad -; Wire_Pad_2.0x3.0
SW1: SKRPACE010 side tact; SW_SKRPACE010_4.2x3.2
TL1: REAR strip pad (3V3); FPC_Pad_1.2x0.6
TL2: REAR strip pad (GND); FPC_Pad_1.2x0.6
TL3: REAR strip pad (I2C_SDA); FPC_Pad_1.2x0.6
TL4: REAR strip pad (I2C_SCL); FPC_Pad_1.2x0.6
TP1: VMOT; TP_Pad_D0.8
TP2: STCK_DRV; TP_Pad_D0.8
TP3: SUP_TXD; TP_Pad_D0.8
TP4: SUP_RXD; TP_Pad_D0.8
TP5: MOT_EN_FAULT; TP_Pad_D0.8
TP6: ARM_CLK; TP_Pad_D0.8
U1: ISP1807-LR (consigned); ISP1807
U2: XC6206P332MR-G; SOT-23
U3: MCP73832T-2ACI/OT; SOT-23-5
U4A: DRV5032AJDMRR; DRV5032_X2SON-4_DMR0004B
U5: TPL5010DDCR; SOT-23-6
U6: SN74AUP1G74DCUR; VSSOP-8_2.3x2mm_P0.5mm
U7: STSPIN220; QFN-16-1EP_3x3mm_P0.5mm_EP1.7x1.7mm
U8: TPS61023DRLR; SOT-563
U9: INA180A1IDBVR; SOT-23-5
U11: TLV7011DCKR; SOT-353_SC-70-5
U30: STM32C011F4U6; UFQFPN-20_3x3_P0.5
U31: SN74AUP1G08DCKR; SOT-353_SC-70-5
U32: TP74AUP1G08S5 (AND); SOT-353_SC-70-5
UU1: USBLC6-2SC6; SOT-23-6

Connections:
3V3: C1.1, C2.1, C7.1, C14.1, C28.1, C50.1, C51.1, C52.1, R1.1, R19.1, R21.1, R40.1, R49.1, R67.1, R68.1, R80.2, TL1.1, U1.26, U2.2, U4A.1, U5.1, U6.2, U6.7, U6.8, U11.5, U30.4, U31.5, U32.5
ARM_CLK: R29.1, TP6.1, U1.43, U6.1, U30.7
BLD: QD3.3, QD4.3, R24.2, R25.2
BST_FB: R55.2, R56.1, U8.6
BST_SW: L1.2, U8.3
BTN_N: SW1.1, SW1.2, U1.37
BUZ_A: QD5.5, RDA.1, U1.51
BUZ_B: QBB.1, RDB.1, U1.52
CC1: JU1.A5, RU1.1
CC2: JU1.B5, RU2.1
CHG_P2: R3.2, R4.1
CHG_PROG: R3.1, U3.5
CHG_STAT: D5.1, U1.48, U3.1
CH_TOP: QD1.6, R11.2
DOCKED_H: QD2.3, QD3.2, QD5.6, R21.2, U1.44, U30.20
DOCK_N: QD5.2, R19.2, U1.3, U4A.4
DOCK_TEST: QD2.5, R22.1, U1.50
GND: C1.2, C2.2, C5.2, C6.2, C7.2, C9.2, C10.2, C14.2, C19.2, C20.2, C21.2, C22.2, C23.2, C24.2, C25.2, C27.2, C28.2, C31.2, C32.2, C50.2, C51.2, C52.2, CB1.2, CB2.2, CB3.2, CU1.2, CU2.2, DU1.2, DZ1.2, J13.1, JU1.A1, JU1.A12, JU1.B1, JU1.B12, JU1.SH, QBB.2, QD1.4, QD2.4, QD3.1, QD3.4, QD4.1, QD4.4, QD5.1, QD5.4, R4.2, R7.2, R16.2, R17.2, R18.2, R22.2, R26.2, R27.2, R29.2, R34.2, R35.2, R36.2, R38.2, R39.2, R43.2, R51.2, R56.2, R58.2, R81.2, R82.2, R86.2, RDA.2, RDB.2, RU1.2, RU2.2, RU3.2, SP2.1, SW1.3, SW1.4, TL2.1, U1.1, U1.7, U1.14, U1.16, U1.18, U1.21, U1.23, U1.24, U1.25, U1.31, U2.1, U3.2, U4A.2, U4A.5, U5.2, U6.4, U7.7, U7.15, U7.16, U7.17, U8.2, U9.2, U11.2, U30.5, U30.21, U31.3, U32.3, UU1.2
I2C_SCL: R68.2, TL4.1, U1.39
I2C_SDA: R67.2, TL3.1, U1.41
INA_OUT: R48.1, U9.1
I_SENSE: C27.1, R48.2, U1.38, U11.3
LATCH_CLR_N: U6.6, U32.4
LATCH_Q: QD1.2, R17.1, U1.4, U6.5
LED_B: R76.1, U1.42
LED_B_K: LD1.3, R76.2
LED_G: R75.1, U1.6
LED_G_K: LD1.2, R75.2
LED_R: R74.1, U1.53
LED_R_K: D5.2, LD1.1, R74.2
MCU_EN: QD2.2, R18.1, U1.45, U30.1
MOT_A1: J1.4, U7.3
MOT_A2: J1.2, U7.5
MOT_B1: J1.3, U7.10
MOT_B2: J1.1, U7.8
MOT_DIR: QD4.2, R16.1, U1.33, U7.1, U30.9
MOT_EN_FAULT: C20.1, R40.2, TP5.1, U1.35, U7.13
MOT_REF: C19.1, R37.2, R38.1, U7.11
MOT_STBY: R37.1, R39.1, U1.32, U7.14
NRST: J12.1, R1.2, U1.13, U30.14
OC_OK: U1.2, U11.1, U30.10, U32.2
OC_REF: R49.2, R50.1, U11.4
OC_REF2: R50.2, R51.1
PGATE: C11.1, Q4.1, QD3.5, R9.2, R10.2, R11.1
PGATE2: C60.1, Q15.1, QD4.5, R83.2, R84.1
PG_A: QD1.1, QD2.6
PG_B: QD2.1, QD3.6, QD4.6
PZ_A: PZ1.1, QD5.3, RBA.2
PZ_B: PZ2.1, QBB.3, RBB.2
QS_D: QD1.3, R84.2
RF_BRIDGE: U1.20, U1.22
SNSA: R34.1, U7.4
SNSB: R35.1, U7.9
STCK_DRV: TP2.1, U7.2, U31.4
STCK_MCU: R43.1, U1.34, U30.8, U31.1
SUP_DONE: U5.4, U30.2
SUP_NRST: J16.1, R80.1, U5.6, U30.6, U32.1
SUP_OK: U1.5, U30.13
SUP_PERMIT: QD1.5, R82.1, U30.12
SUP_RXD: TP4.1, U1.29, U30.17
SUP_STCK_EN: R81.1, U30.11, U31.2
SUP_SWDCLK: J15.1, U30.19
SUP_SWDIO: J14.1, U30.18
SUP_TXD: TP3.1, U1.27, U30.16
SUP_WAKE: U5.5, U30.3
SWDCLK: J11.1, U1.30
SWDIO: J10.1, U1.28
TOFF: R36.1, U7.12
USB_DM: JU1.A7, JU1.B7, U1.10, UU1.3, UU1.4
USB_DP: JU1.A6, JU1.B6, U1.8, UU1.1, UU1.6
VBAT: C5.1, C6.1, C9.1, C11.2, LD1.4, Q4.2, R6.1, R9.1, R10.1, RBA.1, RBB.1, SP1.1, U2.3, U3.3
VBAT_SENSE: C10.1, R6.2, R7.1, U1.36
VBUS_G: QU1.1, RU3.1
VBUS_P: CU1.1, QU1.2, R85.1, U1.12, U3.4
VBUS_R: CU2.1, DU1.1, JU1.A4, JU1.A9, JU1.B4, JU1.B9, QU1.3, UU1.5
VBUS_SENSE: R85.2, R86.1, U1.46
VMOT: C21.1, C22.1, C23.1, R44.2, R57.1, TP1.1, U7.6, U9.4
VMOT_A: C60.2, Q4.3, Q15.2, R83.1
VMOT_PRE: C31.1, CB1.1, CB2.1, CB3.1, DZ1.1, R24.1, R25.1, R44.1, R55.1, U8.5, U9.3
VMOT_RAW: C24.1, C25.1, L1.1, Q15.3, U8.1, U8.4, U9.5
VMOT_SENSE: C32.1, R57.2, R58.1, U1.40
WDT_DELAY: R26.1, R27.1, U5.3
